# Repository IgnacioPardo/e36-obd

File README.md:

<div align="center">

# E36 OBD

**Read a pre-OBD2 BMW's brain — from a Mac, an iPhone, an Apple Watch, or a board you build yourself.**

A 1994 BMW E36 316i (M43B16, Bosch Motronic 1.7.2) predates OBD2. It speaks **KWP71** over a single-wire **K‑line**, woken with a 5‑baud slow init. A generic OBD2 scan tool can't talk to it at all — not "fewer PIDs", it will *never* establish a session. The usual answer is a Windows laptop running INPA. This isn't that: it's a Mac client, a native iOS/watchOS app, ESP32 firmware, and two open hardware builds — all offline, no Windows, no VM, no third‑party dependencies.

</div>

---

## Four ways to read the car

| | Component | What it is | Where |
|---|---|---|---|
| 🖥️ | **macOS client + web panel** | ~600 lines of Python (stdlib + `pyserial`) driving an FTDI K‑line cable through Apple's built‑in `AppleUSBFTDI` — the 5‑baud wakeup is bit‑banged with the UART's BREAK control. CLI **and** a local web dashboard. | [`e36obd/`](e36obd/) · [client reference](#-macos-client--web-dashboard) |
| 📱 | **iOS + Apple Watch app** | Native SwiftUI BLE dashboard: authentic E36 instruments, a real‑time 3D car, DME fault reading, session recording to SQLite, CSV export, widgets, CarPlay and Live Activities. No servers, no internet. | [`ios/`](ios/) · [details](#-ios--apple-watch-app) |
| 🔌 | **ESP32‑S3 firmware** | MicroPython K‑line ⇄ BLE bridge (Nordic UART) that the app talks to. Plus an Arduino reference sketch and a WiFi/PWA fallback. | [`firmware/`](firmware/) · [details](#-firmware-esp32-s3) |
| 🧩 | **Onboard board (rev B)** | A custom single PCB — ESP32‑S3 + L9637D + AP63203 buck + an OBD2 plug — that plugs straight into the car, in a printed case with a machined‑look **=BMW=** badge. | [`hardware/onboard/`](hardware/onboard/) · [details](#-hardware) |
| 🛠️ | **ELM backpack (rev E)** | A printed enclosure that turns a gutted ELM327 + an ESP32 DevKit into an inline reader — the salvage build the custom board replaces. | [`hardware/elm-backpack/`](hardware/elm-backpack/) · [details](#-hardware) |

---

## Why it's hard (and what was learned on the car)

K‑line‑only BMWs (E36, E38, E39, early E46) expect the diagnostic K‑line on **OBD2 pin 7**, wake on a **5‑baud** address, and run **KWP71**: framed blocks `[length][seq][title][payload…][0x03]` where *every byte but the last* is acknowledged by its bitwise inversion, in both directions. There is no error recovery — one bad byte ends the session.

This was **verified end‑to‑end on a 1994 E36 M43B16 automatic** (2026‑08‑09). The findings that cost the most to discover:

- **The L‑line jumper is mandatory.** A stock K+DCAN cable drives only OBD2 pin 7, but the 1.7‑era DME wants the 5‑baud wakeup on the **L‑line** (OBD2 pin 15). The fix is a solder bridge between **pins 7 and 15** — the instant it was in, address `0x10` answered `55 00 81`. (Watch pin 16: it's +12 V.)
- **Address is `0x10`** (BMW Motronic DME), not `0x12` (that's DS2, a different protocol).
- **Live values only populate with the engine running** — key‑on/engine‑off reads all zeros and looks exactly like a dead link.
- **Sampling is round‑trip bound** at ~1 Hz over 9600 baud, so a log's silence is not proof a sub‑second glitch didn't happen.
- **Reads degrade with the engine running** — ignition noise corrupts the byte handshake, so the live path collapses the core sensors into one contiguous 11‑byte read and rebuilds the session when it breaks.

> 📎 Full pre‑flight electrical checklist, the discovery method for un‑mapping sensors, and protocol notes are in [the client reference below](#-macos-client--web-dashboard) and [`docs/PROTOCOL_NOTES.md`](docs/PROTOCOL_NOTES.md).

---

## 📱 iOS + Apple Watch app

[`ios/E36OBD.xcodeproj`](ios/) — a native SwiftUI dashboard that reads the car over **BLE**, with no server and no internet. iOS 18+, watchOS 11+, **zero third‑party dependencies** (SQLite is the system `libsqlite3`; everything else is Apple's own frameworks).

<table>
<tr>
<td width="60%"></td>
<td width="40%"></td>
</tr>
<tr>
<td align="center"><em>Instruments — the E36 cluster, rebuilt</em></td>
<td align="center"><em>Auto — vehicle, reader state, latest readings</em></td>
</tr>
</table>

**What it does**

Latest development handoff: [session context, design decisions, validation and installation state](docs/sessions/2026-09-11-app-scene-companions.md).

- **Instruments** — the classic 90s BMW cluster in portrait and landscape: load (ms) and tach dials with the red zone, battery/coolant gauges, amber 7‑segment readouts, fan‑out auxiliaries. Needles ease to each reading without interpolating stored samples. Saturated 2550 rpm and empty‑RAM reads are called out as **DME sin datos** rather than shown as real values.
- **Auto** — a real‑time **3D render of the owner's 316i in 295 Samoablau Metallic**, drawn on‑device with RealityKit + Metal. Normal tabs keep the whole car in frame. Expand the scene for free navigation: one finger orbits horizontally and vertically, two fingers pan the camera, and pinch moves from detail close-ups to distant views without auto-fit pushing back. Zoom and pan can be combined; the chosen distance and position survive device rotation. The reset button or double-tap restores the front view, and closing the scene restores protected dashboard framing. Paint, glass and reflections are computed on the phone; the sun button selects studio or outdoor surroundings.
- **Navigation** — Auto, Fallas, Sesiones and Ajustes share one persistent scene, above their content in portrait and beside it in landscape. Each tab is the next quarter-turn around the car; moving back through the bar reverses that ordered orbit, including when tabs are skipped. The scene reaches the screen edge; text and controls retain readable insets. En vivo, Instrumentos and BLE stay at the top. Starting capture keeps the current tab; closing Instruments returns to it. Session selection and unsaved settings survive navigation.
- **Faults** — reads the DME fault memory; pauses and resumes the same recording session around the read.
- **Sessions** — every capture recorded to local SQLite (WAL, file‑protected), browsable with a shared cursor across all five channels and **CSV export** of sensors + events. Gaps are never bridged.
- **Alerts** — configurable thresholds (low load, coolant, intake) with hysteresis, sound and haptics; every episode is logged even when sound is rate‑limited.
- **Widgets · CarPlay · Watch · Live Activities** — *Instrumento E36*, *Garage E36* (with the car render) and *OBC E36* widgets for the Home Screen, StandBy and CarPlay. Garage and OBC also have a large Home Screen size with all five readings; a watchOS companion with five full‑screen gauges and complications; and a Live Activity on the Lock Screen and Dynamic Island. The ESP32 keeps a single BLE link to the phone; everything else is fed from it.

<table>
<tr>
<td></td>
<td></td>
</tr>
</table>

**Architecture.** The tested, platform‑independent core is a local Swift package, [`ios/Core`](ios/Core) (`E36Core`), so the hard parts run without a simulator:

| Module | Responsibility |
|---|---|
| `AcquisitionMachine` | pure state machine for BLE capture (sync → idle → live, faults, DME recovery) |
| `WireProtocol` | frames raw bytes into lines before UTF‑8; parses telemetry vs text |
| `SessionStore` | an `actor` owning the sole SQLite connection; records off the UI/BLE threads; CSV export |
| `AlertEngine` | threshold rules with hysteresis |
| `Models` · `GraphSeries` · `WidgetSnapshot` · `CompanionSnapshot` | sensor model, downsampling that keeps extrema/events, and the bounded snapshots shared to widgets and the watch |

```sh
open ios/E36OBD.xcodeproj          # E36OBD Demo runs on the simulator (scenario picker, no BLE radio)
swift test --package-path ios/Core # 19 core tests, no simulator needed
```

The Xcode project is generated, not hand‑edited — `python3 ios/tools/generate_project.py` regenerates it with the stdlib alone. Deeper docs: **[`ios/DESIGN.md`](ios/DESIGN.md)** (instrument design), **[`ios/VALIDATION.md`](ios/VALIDATION.md)** (QA log), **[`ios/WIDGETS.md`](ios/WIDGETS.md)**, **[`ios/WATCH_AND_LIVE_ACTIVITIES.md`](ios/WATCH_AND_LIVE_ACTIVITIES.md)**, and the 3D pipeline in **[`ios/Design/Vehicle/`](ios/Design/Vehicle/)**.

---

## 🔌 Firmware (ESP32‑S3)

The board runs **MicroPython** (`ESP32_GENERIC_S3‑SPIRAM_OCT`, v1.29.0). On boot, [`firmware/mp/main.py`](firmware/mp/main.py) does `import ble; ble.arrancar()`, starting the BLE loop on its own thread so attaching the REPL doesn't kill it.

| Module | Role |
|---|---|
| [`firmware/mp/kline.py`](firmware/mp/kline.py) | KWP71 transport: 5‑baud slow init, block send/recv with inverted acks, RAM reads, sensor + fault decode. Drives the **ST L9637D** on `TX=GPIO17`, `RX=GPIO18`. DME at **9600 baud** (`0x10`); the automatic gearbox EGS at **4800 baud** (`0x6C`). |
| [`firmware/mp/ble.py`](firmware/mp/ble.py) | The BLE "panel": Nordic UART service, command loop, live streaming, fault reads, session lifecycle and desktop‑grade recovery. |
| [`firmware/mp/web.py`](firmware/mp/web.py) | Optional WiFi SoftAP dashboard (`E36-OBD` / `192.168.4.1`), not started at boot. |
| [`firmware/kline_e36/kline_e36.ino`](firmware/kline_e36/) | An Arduino/C++ reference port of the same protocol — a bring‑up sketch that inits and reads faults once over USB serial. |

**BLE contract** — advertises the **name only** (`E36-OBD`); the app verifies Nordic UART after connecting.

```text
service 6E400001-B5A3-F393-E0A9-E50E24DCCA9E   RX 6E400002-… (write)   TX 6E400003-… (notify)
commands (1 ASCII char): v = live · f = faults · s = stop · ? = help
live line:  D <rpm> <load_ms> <coolant_C> <battery_V> <query_ms> [intake_C]
            D 930 0.70 63.1 13.48 341 23.7
```

Output is CRLF, chunked ≤20 bytes with 12 ms between notifications; intake temp is appended last so older clients stay compatible. **Update firmware over USB** with [`ios/tools/update_ble.py`](ios/tools/update_ble.py) (via `mpremote`) — it backs up every target file, verifies it's really the E36 reader, writes, reads back, and rolls back on any mismatch. It never reflashes MicroPython or touches `main.py`.

Host‑run tests in [`firmware/tests/`](firmware/tests/) exercise the real modules against a scripted fake UART / mocked radio — including a byte‑for‑byte match against the desktop client:

```sh
python3 -B -m unittest discover -s firmware/tests -v
```

---

## 🧩 Hardware

Two open builds, both parametric — a Python source file generates the board or the case, verified by script before export.

### Onboard board — rev B (`hardware/onboard/`)

One 90 × 50 mm two‑layer PCB for JLCPCB SMD assembly: **ESP32‑S3‑WROOM‑1 + L9637D + AP63203 buck + a PCB‑mount OBD2 plug**. 3.3 V straight from the car's 12 V, a hardware low‑battery cutoff (buck EN divider: on at 12.5 V, off at 11.5 V), and it plugs directly into the E36's 20‑pin round connector via a pigtail. `gen_board.py` is the source of truth — placement, nets, zones and the custom OBD2 footprint; `export.py` runs DRC and emits gerbers/BOM/CPL. **DRC: 0 errors.**

<table>
<tr>
<td></td>
<td></td>
</tr>
<tr>
<td align="center"><em>The board — ESP32‑S3 + L9637D + buck + OBD2</em></td>
<td align="center"><em>The case — =BMW= badge, light‑guide LED, USB‑C</em></td>
</tr>
</table>

`case.py` generates a three‑piece printed enclosure (96.8 × 56 × 27 mm): black base and lid with R6 corners, 45° chamfers and a shadow line at the seam, plus a separate **=BMW= badge** copied from the M50 valve cover — black field, 13 fine silver ribs running the length of the lid, the "BMW" plaque set toward the plug and cutting only the middle ribs (one filament change at 1.6 mm, or two colours via AMS). The OBD2 plug's neck is clamped in the end wall, the USB‑C shell passes through a shell‑shaped opening flush with a bezel, LEDs come out through Ø3 mm light pipes, RESET/BOOT are clip holes, and four M3 × 12 screws from below thread into brass heat‑set inserts — nothing visible on the outside. `CASE_PIGTAIL=1` builds the variant without the OBD2 plug for a direct 20‑pin pigtail. See [`hardware/onboard/README.md`](hardware/onboard/README.md) for the full BOM, the schematic, the pinout, the print list and the pre‑fab checklist. ([schematic](hardware/onboard/fab/schematic.png))

### ELM backpack — rev E (`hardware/elm-backpack/`)

The predecessor build: a 162 × 48 × 30.4 mm printed inline enclosure that houses a gutted ELM327 + a buck + an ESP32‑S3 DevKit end‑to‑end, with the same ribbed BMW lid. Fully parametric (`model.py` on build123d), with an offline interactive [CAD viewer](hardware/elm-backpack/viewer.html) and print‑ready 3MF/STL.

Details, the parts list and print settings: [`hardware/elm-backpack/README.md`](hardware/elm-backpack/README.md).

---

## 🖥️ macOS client & web dashboard

Pure Python — stdlib plus `pyserial`. It drives an FTDI **FT232R "INPA compatible K+DCAN"** cable through the OS's own `AppleUSBFTDI` (no vendor kext), bit‑banging the 5‑baud init with the UART's BREAK control. From the repo root:

```bash
python3 -m venv .venv && ./.venv/bin/pip install pyserial   # first time
./.venv/bin/python -m e36obd doctor                         # desk test, no car
```

**Command line** — run in order; each only makes sense once the previous worked:

| Command | What it does |
|---|---|
| `doctor` | Lists serial ports, flags the FTDI one, toggles BREAK, listens 2 s. Silence with no car is fine. |
| `scan` | Tries candidate addresses (`0x10` first) and reports which return a `0x55` sync + keywords. |
| `id` | Prints the ECU identification strings — the real proof of a working link. |
| `codes` | Reads stored fault codes (raw hex; a *speculative* 5‑byte grouping is not a verified decode). |
| `log` | Live values to CSV — `--adc`, `--ram ADDR:LEN`, `--param`, `--interval`, `--duration`, `--out`. |
| `raw` | Sends an arbitrary block title with optional payload — for hunting non‑standard commands. |
| `clear` | Erases fault memory (prompts). **Destroys evidence — read and save codes first.** |

Global flags go **before** the subcommand: `--port`, `--baud` (9600), `--address` (`0x10`), `--loopback auto|on|off`, `-v`. Example: `./.venv/bin/python -m e36obd --address 0x10 -v id`.

**Web dashboard** — `dash` serves a local panel (stdlib + `pyserial`, no framework/CDN, works offline). One thread owns the serial port and drains an action queue between samples, so recording, re‑reading faults, dumping RAM and probing the gearbox coexist with live polling without fighting over the line.

```bash
./.venv/bin/python -m e36obd dash            # http://127.0.0.1:8036
./.venv/bin/python -m e36obd dash --lan      # reachable from the phone, token-guarded
./.venv/bin/python -m e36obd dash --demo     # synthetic data, no car
```

Four hash‑addressable tabs — **Tablero** (analog instruments + 4‑min trend), **Diagnóstico** (decoded faults, DS2 gearbox probe, before/after snapshots), **Capturas** (recorded sessions with a shared cursor and two‑session overlay), **Scanner** (RAM explorer with cumulative change detection). Write and actuator blocks (`0x02` WriteRAM, `0x1A` WriteEEPROM, `0x04` ActivateActuator) are blocked **in the server**, verified against a simulated ECU. There's also a Web Bluetooth **PWA** in [`docs/ble/`](docs/ble/).

<details>
<summary><strong>Pre‑flight electrical checklist</strong> — read this before the cable ever touches the car</summary>

Almost every "it doesn't work" report is one of these three, and all three fail *silently* — the port opens, the command runs, and nothing answers.

1. **OBD2 pins 7–8 must be bridged.** K‑line‑only BMWs expect the K‑line on pin 7; many cables/adapters present it on pin 8. Set the cable's K‑line switch, or solder 7↔8 on its PCB. Verify with a multimeter in continuity: probe pin 7 and pin 8 on the cable's own 16‑pin connector — it should beep.
2. **The 20‑pin adapter must be fully pinned.** The cable is bus‑powered from OBD2 pin 16 (+12 V from the car). Cheap adapters wired K‑line‑and‑ground only leave the FTDI chip unpowered. Confirm it passes at minimum K‑line, +12 V and ground.
3. **Multimeter checks — verify, don't trust.** Confirm the 20‑pin round pinout against a BMW source (TIS / service manual) before probing; several conflicting diagrams circulate. Do continuity with the harness **disconnected from the car**; do voltage at the car's connector with nothing else plugged in.

| Check | Meter mode | Expected |
|---|---|---|
| Battery at the round connector's +12 V pin | DC volts, black on chassis ground | ~12.4 V off, ~13.8–14.4 V running |
| Round K‑line pin → OBD2 pin 7 | Continuity, unplugged from car | Beeps / ~0 Ω |
| Round +12 V pin → OBD2 pin 16 | Continuity, unplugged | Beeps / ~0 Ω |
| Round ground pin → OBD2 pins 4 and 5 | Continuity, unplugged | Beeps on both |
| OBD2 pin 7 → pin 8 on the cable itself | Continuity | Beeps (see §1) |

4. **Ignition position 2.** The DME is only awake with the ignition in position 2 (dash lights on, engine not running). Position 1 is not enough; nothing answers with the key out.

</details>

<details>
<summary><strong>Discovering what the values mean</strong> — ADC channels and the RAM map are un‑mapped</summary>

`log` is a **discovery tool**, not a dashboard: there's no table saying which channel is coolant or where the TPS lives, and raw ADC bytes are not degrees. The method is empirical — change **one** thing with a known physical effect, then find the column that moved the same way.

- **Coolant temp** — log a full sweep through a cold‑start warm‑up; it's the channel that moves *monotonically* over ~10 min then flattens (NTC sensors often fall as temp rises).
- **Throttle** — engine off, ignition on; sweep the pedal. TPS tracks the pedal, returns to rest, and hits a ceiling at wide‑open.
- **Battery** — calibrate absolutely against the multimeter; two points give a linear scale and often hint at the shared ADC reference.
- **Intake air** — responds within seconds to a heat gun, unlike coolant's minutes of lag.

Prefer monotonic or repeatable‑cycle stimuli, load the CSV into anything that plots, then re‑log the interesting channels at a shorter interval. **Nothing here persists a mapping for you — write down what you confirm.**

</details>

<details>
<summary><strong>Troubleshooting</strong></summary>

| Symptom | Likely cause | What to do |
|---|---|---|
| `No serial port found` | Cable not enumerated, or macOS hasn't claimed it | `ls /dev/cu.*`; try another USB port/cable; `system_profiler SPUSBDataType`; pass `--port`. |
| `doctor` opens the port but BREAK fails | `/dev/tty.*` selected instead of `/dev/cu.*`, or a vendor FTDI kext interfering | Always use `/dev/cu.*`; uninstall any vendor FTDI driver and reboot. |
| `scan` finds no responding address | Almost always electrical | Work the pre‑flight list in order before widening the address set. |
| Init OK but blocks fail their ack — `bad ack for byte N` | Timing / line quality, or non‑standard framing | Re‑run with `-v`; try a shorter adapter; if always byte 0, force `--loopback on|off`. |
| Session establishes then dies mid‑`log` | KWP71 drops the link if blocks stop; also a loose‑connection signature | Lower `--interval`, fewer channels; then check the physical connection. |
| Disconnects worse with the engine running | Ignition noise on a single‑wire bus, or a sagging supply | Route away from plug leads/coil; verify pin‑16 voltage running; clean ground. |
| `NOT_SUPPORTED` | BMW used a different block title | Probe with `raw --title 0xNN`. |

</details>

<details>
<summary><strong>Known vs unknown</strong> — how much to trust the output</summary>

**Solid:** KWP71 framing and acks (from [colinbourassa/libiceblock](https://github.com/colinbourassa/libiceblock)); the macOS BREAK‑banged 5‑baud init (absolute bit deadlines, the port never leaves 9600); loopback auto‑detection.

**Not confirmed:** exact block titles may be non‑standard per manufacturer; the fault‑code record layout and code→description mapping are **not** decoded (a code number without a table tells you a fault exists, not what it is); ADC channel meanings, the RAM map and scaling are unknown and must be derived. `raw` and `log` exist precisely to explore this.

</details>

---

## Repository layout

```
e36obd/         macOS client + web dashboard (Python: stdlib + pyserial)
firmware/       ESP32-S3 firmware — mp/ (MicroPython, shipping) + kline_e36/ (Arduino ref) + tests/
ios/            SwiftUI iOS + watchOS app — E36OBD.xcodeproj, Core/ (E36Core package), Design/Vehicle/ (3D)
hardware/       onboard/ (rev B custom PCB + case) · elm-backpack/ (rev E enclosure) · wiring diagrams
docs/           PROTOCOL_NOTES.md, EGS_NOTES.md, GAUGE_DESIGN.md, cableado.html, ble/ (Web Bluetooth PWA)
sessions/       archived AI-assisted development transcripts (Git LFS)
```

Large binary assets (`.usdz`, `.blend`, `.glb`, `.exr`, `.step/.stl/.3mf`, `.pdf`, session logs) are tracked with **Git LFS** — install [git‑lfs](https://git-lfs.com) and `git lfs pull` to fetch them.

## Safety

- **Do not probe pins at random with the ignition on.** Shorting a DME input to +12 V or ground can destroy it, and not every line is fuse‑protected. An M1.7.2 is expensive and increasingly rare.
- Do continuity testing with the harness **disconnected from the car**; do voltage testing one pin at a time against a known‑good ground.
- **Verify the round‑connector pinout against a BMW source before touching a probe to it.** Assume any diagram — including in this repo — is wrong until you've checked it. Beware pin 16 (+12 V) next to the K‑line.
- **`clear` and fault‑memory erase destroy evidence.** Read and save codes first; the web panel always snapshots before erasing.
- `raw` sends arbitrary block titles to a live engine controller. `WRITE_RAM`, `WRITE_EEPROM` and `ACTIVATE_ACTUATOR` are not read‑only. Know what a title does before sending it.
- Do first‑contact work engine‑off. Once logging with the engine running, keep the cable clear of the belts, fan and exhaust manifold.

---

<div align="center">
<sub>Personal project for a specific 1994 E36 316i (M43B16). No affiliation with BMW; "BMW" marks belong to their owner and the badge/branding here are for a personal build. No formal license — ask before reuse.</sub>
</div>

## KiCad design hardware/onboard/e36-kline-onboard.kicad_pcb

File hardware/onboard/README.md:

# E36 K-line — una sola placa (rev B)

ESP32-S3-WROOM-1 + L9637D + buck AP63203 + ficha OBD2 macho, todo en una PCB de **90 × 50 mm**,
dos capas, para mandar a JLCPCB con ensamblado SMD. Reemplaza al conjunto "ELM327 destripado +
DevKitC-1 + módulo buck" y a la placa `../kline-frontend.kicad_pcb` (que dejaba el MCU afuera).

| Archivo | Qué es |
|---|---|
| `gen_board.py` | **La fuente.** Colocación, redes, clases de pista, footprint OBD2, zonas, serigrafía. Genera la placa. |
| `e36-kline-onboard.kicad_pcb` / `.kicad_pro` | Placa generada y ruteada (abrir en KiCad 10). |
| `e36obd.pretty/OBD2_Male_RightAngle_16P.kicad_mod` + `fp-lib-table` | Footprint propio de la ficha OBD2. |
| `gen_schematic.py` → `schematic.svg`, `e36-kline-onboard.net` | Esquema y netlist, generados de **las mismas redes** que la placa y verificados contra ellas. |
| `export.py` → `fab/` | DRC, gerbers (`e36-kline-onboard-gerbers.zip`), `bom-jlcpcb.csv`, `cpl-jlcpcb.csv`, renders. |
| `pricing.py` → `fab/pricing-jlcpcb.md` | Estimación de precio JLCPCB (API de partes + tarifas publicadas): partes, fijos, totales por cantidad. |
| `pcbway.py` → `fab/pcbway/`, `fab/pcbway-sample-order.zip` | Paquete de pedido PCBWay para 1 muestra ensamblada: BOM en su formato con MPN, centroides, dibujo de armado, notas y parámetros del formulario. |
| `case.py` → `case/` | Caja de dos piezas (STL listos para imprimir, STEP, ensamble con referencias). |
| `render_case.py` → `case/render-*.png` | Renders en Blender de la caja con la placa real (GLB exportado por kicad-cli) adentro. |

Estado: **DRC 0 errores, 0 desconexiones** (KiCad 10.0.5). Quedan solo avisos de serigrafía
(referencias de 0603 que pisan pads); JLC los recorta solos.

## Qué hay en la placa

```
 OBD2 16 ─ F1 1A ─┬─ D1 TVS SMBJ24A ─ GND
                  ├─ R1 510R ─ K ─── OBD2 7 y 15 ──┐
                  ├─ U1 L9637D VS        K ────────┘   RX → GPIO18   TX ← GPIO17
                  ├─ R2 100k / R3 22k ── V_SENSE → GPIO4 (ADC1)
                  ├─ R10 36k / R11 3k74 ─ EN del buck (UVLO: ON 12,5 V, OFF 11,5 V)
                  └─ D2 SS34 ─┬─ VIN ─ U2 AP63203 ─ L1 4.7µH ─ 3V3 ─ ESP32-S3-WROOM-1-N16R8
 USB-C VBUS ─ D3 SS34 ────────┘  └ R12 4k7 → EN (con USB arranca siempre)   │
 USB-C D+/D- ─────────────────────────────────────────── GPIO20/19 ┘
 J4 (cola al redondo de 20): 1 GND · 2 K · 3 +12   — en paralelo con la ficha OBD2
```

- **3,3 V directo desde los 12 V**, sin riel de 5 V. El único consumidor de 5 V era el DevKit.
  El AP63203 (3,8–32 V de entrada, 2 A, salida fija 3,3 V, 1,1 MHz) alimenta módulo y L9637D.
  FB va directo a 3V3 (versión de salida fija).
- **Corte por batería baja, en hardware.** El pin EN del buck tiene umbral de precisión (1,18 V
  sube / 1,10 V baja) y dos fuentes de corriente internas (1,5 µA fija + 4 µA de histéresis).
  Con R10 = 36k desde VBAT_F y R11 = 3,74k a GND (Eq. 1 y 2 de la hoja de datos) el buck
  **arranca a 12,5 V y corta a 11,5 V**: con el motor andando (13,1–14,4 V) está siempre
  encendido; con el motor parado sigue hasta que la batería baja a 11,5 V y ahí se apaga solo,
  quedando el consumo en ~1 mA (1 µA del buck apagado + los divisores + el reposo del L9637D).
  R12 = 4k7 desde VBUS fuerza EN por encima del umbral: **con USB arranca siempre**, haya auto
  o no. La ventana entre batería en reposo (12,6–12,8 V) y alternador flojo (13,1 V) es
  demasiado angosta para detectar "motor parado" solo con resistencias, así que el corte
  duro es el piso de seguridad: lo que evita el drenaje diario es el **deep sleep por
  V_SENSE** en el firmware (dormir por debajo de ~12,9 V unos minutos, despertar y medir).
  Para otros umbrales: `R10 = (0,932·VON − VOFF)/4,1 µA`, `R11 = 1,1·R10/(VOFF − 1,1 + 5,5 µA·R10)`.
- **USB-C solo para programar y para el banco**: VBUS y los 12 V del auto se OR-ean por D2/D3 hacia
  VIN. Con el auto y la notebook enchufados a la vez mandan los 12 V; nada vuelve a la notebook.
  Sin auto, la línea K y V_SENSE están muertas; el ESP32 arranca igual.
- **L9637D** igual que el prototipo que funcionó: VCC a 3,3 V (mínimo 3 V, lógica compatible
  sin conversor), VS a los 12 V filtrados, K a los pines **7 y 15** (el DME despierta por L).
  R1 510 Ω es el pull-up de K a VS que exige la hoja de datos. A 14 V disipa 0,38 W mientras K
  está baja, así que va en **2010** (0,75 W), no en 0805 como en la placa anterior.
- **D1 con la banda hacia +12 V.** En `../kline-frontend` el TVS estaba al revés en el netlist
  (ánodo a +12 V): conduciría a 0,7 V y volaría el fusible. Acá pad 1 (cátodo) = VBAT_F.
  Polaridad invertida del auto → el TVS conduce en directo y F1 corta. Ese es el mecanismo.
- **Sensado de batería**: 100k/22k → 16 V = 2,88 V en GPIO4. `V = 3,3 × adc/4095 × 122/22`.
  El firmware de hoy no lo lee (la tensión viene del DME por K); queda para dormir el módulo
  cuando el motor está parado — el pin 16 es +12 V **permanente**.
- **Módulo entero sobre la placa**, con la antena en el borde superior y una zona prohibida
  (sin cobre, pistas ni vías en las dos caras) de 53–90 × 0–6,5 mm: la opción 2 de la guía de
  Espressif. Se eligió para que la caja sea un prisma liso; la opción 1 (antena colgando) rinde
  algo mejor pero obliga a un saliente. La pared de la caja frente a la antena no puede ser
  metálica ni con carga de carbono.
- **Directo al conector redondo de 20 pines del E36, sin adaptador.** J4 es una JST-XH de 3 vías en
  paralelo con la ficha OBD2: 1 GND, 2 K, 3 +12 V. Se le suelda una cola cortada de un adaptador
  20→OBD2 (o un macho de 20 con cables): **19 → GND, 15+17+20 juntos → K, y el +12 de 16 (KL15,
  ignición) o de 14 (KL30, batería)**. Tomando el +12 del **pin 16** la placa se apaga con la
  llave y el drenaje de batería desaparece del todo; el OBD2 no tiene ese pin, por eso ahí hace
  falta el UVLO y el deep sleep. El macho de 20 no existe para montar en PCB: va por cable. Para
  ese uso, `CASE_PIGTAIL=1 case.py` genera la caja con la pared cerrada y un pasacable de 7 mm en
  vez de la muesca de la ficha.
- **USB: solo el nativo (GPIO19/20), sin puente CH340/CH9102.** Es el puerto "USB" del DevKit, no
  el "COM": MicroPython, `mpremote` y la REPL andan sin tocar nada; grabar la imagen de MicroPython
  exige BOOT apretado al resetear (una vez). Se evaluó poner un CH340C con auto-reset y se descartó
  por innecesario.
- EN: 10k + 1 µF + botón RESET. IO0: 10k + botón BOOT. Programación por el USB nativo
  (GPIO19/20) o por J2 (UART0, sin poblar; pines **EN IO0 TX0 RX0 GND 3V3**). LED verde = 3V3;
  LED ámbar en **GPIO38** (el mismo del RGB del DevKitC-1 v1.1, así el firmware no cambia de pin).

### Pines del ESP32 que usa el firmware

| GPIO | Función | Pin del módulo |
|---|---|---|
| 17 | K_TX → L9637D TX (UART1 + bit-bang del init a 5 baudios) | 10 |
| 18 | K_RX ← L9637D RX | 11 |
| 4 | V_SENSE (ADC1_CH3, funciona con WiFi) | 4 |
| 38 | LED de estado (ámbar) | 31 |
| 0 | BOOT (botón, pull-up 10k) | 27 |
| 19 / 20 | USB D− / D+ | 13 / 14 |
| 43 / 44 | TXD0 / RXD0 → J2 | 37 / 36 |

`firmware/mp/kline.py` sigue con `TX_PIN = 17`, `RX_PIN = 18`: no cambia nada.
En la N16R8 los GPIO 33–37 son de la PSRAM y no se usan.

## La ficha OBD2

Es un macho J1962 acodado de montaje en PCB — el mismo formato que usan los ELM327 y el
**Macchina CCBDM20**. El footprint se construyó desde el STEP y el plano de ese conector,
no de una foto:

| Dato | Valor |
|---|---|
| Paso entre pines de una fila | **4,00 mm** |
| Separación entre filas | **3,00 mm** |
| Fila 1–8 (la de abajo en la cara de enchufe, lado ancho de la D) | 2,25 mm detrás de la brida |
| Fila 9–16 | 5,25 mm detrás de la brida |
| Pata de soldadura | 0,9 × 0,8 mm, ~2,2 mm de largo → agujero 1,3 mm, pad 2,1 mm |
| Cuerpo | 40,3 mm de ancho, todo fuera de la placa; la brida apoya en el borde |

El borde izquierdo de la placa es el plano trasero de la brida. Pin 1 arriba (y = 10 mm),
pin 8 abajo; pines 9–16 en la segunda fila. Solo 4, 5 (GND), 7 (K), 15 (L) y 16 (+12 V) van
a algo; los otros once pads quedan sueltos.

**Antes de soldar el conector**, con la placa sin enchufar al auto, medir continuidad entre
la cara de enchufe y los pads: el pin 16 del macho (esquina, fila de abajo con el lado ancho
arriba, extremo izquierdo mirando los pines) tiene que llegar al pad marcado 16. Si el
conector que compraste está espejado respecto del CCBDM20, el error es **benigno**: +12 V
caería en el pad 9 (sin conectar) y la placa simplemente no encendería. Nada se quema.

## Antes de mandar a fabricar

**Precio** (estimado con `pricing.py`, 2026-09-11, ensamblado económico, sin envío): unas **97 USD por 5 placas
(≈19 c/u)** o **140 USD por 10 (≈14 c/u)**; los fijos son 43 USD (setup 8,18 + stencil 1,53 + 11 partes
extendidas × 3,07) y las partes ≈10 USD por placa, de los cuales el módulo son 5. Detalle en
[`fab/pricing-jlcpcb.md`](fab/pricing-jlcpcb.md). La ficha OBD2 va aparte (sin stock en JLC). Para **una sola muestra
con la ficha soldada por la fábrica**, PCBWay: paquete listo en `fab/pcbway/` (`ORDER-NOTES.md` tiene los valores del
formulario y el texto de instrucciones). **Cotización oficial** del motor de PCBWay (`fab/pcbway/quote-official.md`):
PCB 5 pcs 6,50 USD + ensamblado 1 placa 88,00 USD (tarifa plana) + envío FedEx 48,87 / DHL 72,73; componentes
aparte (≈15–25 USD): ≈160–170 USD la muestra.

1. **Números LCSC.** Los marcados `verificar` o `C?` en `fab/bom-jlcpcb.csv` hay que
   confirmarlos en la librería de JLC al momento de pedir: L9637D (C130489), módulo
   ESP32-S3-WROOM-1-**N16R8** (C2913202), inductor SWPA6045S4R7MT (C78804), TVS SMBJ24A,
   capacitores 1210 10 µF/50 V X7R, la 2010 de 510 Ω y la 0603 de 3,74k (E96). El resto son
   básicos de JLC.
2. **Variante del módulo.** El firmware cargado es `ESP32_GENERIC_S3-SPIRAM_OCT`: necesita
   PSRAM octal → **N16R8** (o N8R8). Una N16 sin R8 arranca pero ese build no.
3. **Ficha OBD2.** J1 es THT: soldarla a mano (patas cortas, estañar desde abajo) o pedir el
   ensamblado TH de JLC (`C9900166046`, "OBD-II-16P-Male-90-Deg", sin plano público:
   verificar su footprint contra la tabla de arriba antes de confiar).
4. **Capacidades JLC**: 2 capas, 1,6 mm, 1 oz. Pista mínima usada 0,187 mm (los cuellos que
   deja Freerouting en los pines finos), holgura mínima 0,15 mm, vía 0,7/0,35, taladro mínimo
   0,3. Todo dentro de lo estándar (0,127 mm / 0,3 mm).
5. **En la vista previa de JLC** revisar la rotación de lo polarizado: D1, D2, D3 (banda),
   LED1/LED2, U1 (pin 1), U2, U3. El CPL sale con el origen en la esquina inferior izquierda.
6. J2 no se puebla (está fuera del BOM y del CPL).
7. La caja es `case.py` (sección **La caja**); la `../elm-backpack` no sirve para esta placa.
8. Si vas directo al conector de 20 pines, no hace falta soldar la ficha OBD2 (J1): con J4 y la
   cola alcanza, y la caja `-pigtail` cierra esa pared.

## La caja

`case.py` (build123d, `~/Desktop/E36_OBD/.cadenv/bin/python hardware/onboard/case.py`) genera
en `case/` una caja de **tres piezas** para **esta** placa, con las mismas coordenadas de
`gen_board.py`: base y tapa en negro y el **emblema =BMW= aparte, en plata**, que encaja a ras
en un cajeado de la tapa. La `../elm-backpack` no sirve: era para las placas sueltas.

| | |
|---|---|
| Exterior | **96,8 × 56,0 × 27,0 mm**, prisma liso, más los 16 mm del conector |
| Forma | esquinas verticales R6, chaflán de 45° de 2 mm en el borde de la tapa y de 1,5 mm en el del piso, línea de sombra de 0,5 mm en la junta; tapa lisa |
| Paredes / piso / tapa | 2,4 / 2,4 / 3,0 mm; la pared del conector 1,5 mm |
| Interior sobre la placa | 17 mm — lo fija la brida del conector (15,6 mm), no la electrónica (máx. 5 mm) |
| Sujeción | 4 × **M3 × 12** desde abajo, cabeza embutida; pasan por los separadores (3 mm) y la placa y roscan en **insertos M3 termofijados** (latón, Ø4,6 × 4,6; agujero impreso Ø4,0 × 5,5) en los postes Ø7,5 de la tapa. Sin tornillos a la vista |
| Variante | `CASE_PIGTAIL=1`: sin muesca para la ficha OBD2, pared izquierda cerrada con pasacable Ø7 para la cola al conector de 20 (`base-pigtail.stl`, `lid-pigtail.stl`) |
| Conector OBD2 | la pared entra en el **cuello de 2 mm** del conector: la brida queda adentro, el cuerpo afuera. La muesca está abierta hacia arriba para bajar la placa; la lengüeta de la tapa la cierra |
| USB-C | **la ficha atraviesa la pared**: sobresale 1,6 mm del borde de la placa y pasa por una abertura con la forma de su blindaje (estadio 9,4 × 3,6, 0,22 de juego por lado) en una pared local de 1,3 mm; la boca queda a ras del fondo de un bisel de 18 × 10 donde entra el sobremoldeado del cable. Una repisa de 1,2 mm bajo el borde de la placa toma el empuje del enchufe |
| Antena | queda dentro, contra la pared trasera: esa pared no puede ser metálica ni con carga de carbono |
| Botones | agujeros Ø2 sobre RESET y BOOT: se pulsan con un clip, no hay botones a la vista (BOOT se movió en la placa a (77,5, 39) para dejar libre la banda del emblema) |
| LEDs | dos **guías de luz**: varilla acrílica Ø3 × 16 mm pegada desde adentro en un agujero Ø3,1 con tope a 0,5 mm de la cara (se ve un punto de Ø2,4) |
| Emblema | pieza aparte `badge.stl`, **85 × 22 × 1,6 mm**, copiada de la tapa M50: campo negro, **13 nervios finos** (0,8 mm de ancho, paso 1,6) que corren a lo largo, y la placa "BMW" **corrida hacia la ficha**, de 12 mm de alto: interrumpe solo los siete nervios del medio; los tres de arriba y los tres de abajo siguen enteros a lo largo, como en el motor. Nervios y letras en relieve de 0,8 mm en plata: se imprime relieve arriba con un **cambio de filamento en la capa de 1,6 mm** (negro → plata) o en dos colores con el AMS. Entra a ras en el cajeado de la tapa con 0,15 de juego por lado; se pega con cianoacrilato |
| Piso | grabado "E36 K-LINE rev B" y el pinout OBD2 |
| Otros | 7 respiraderos por lado (2 × 8 mm), dos ranuras 3 × 12 en el piso para un precinto |

Archivos: `base.stl` (piso abajo), `lid.stl` (**ya dada vuelta**, cara exterior abajo), `badge.stl`
(relieve arriba), `base.step`, `lid.step` (en coordenadas de montaje) y `assembly.step` con la placa,
el módulo, el conector (cuerpo en D real) y los volúmenes de los componentes más altos como referencia.
Los renders (`render_case.py`, Blender EEVEE con tres soles y piso) muestran la ficha OBD2 con su
forma en D. Renders: `render_case.py` (Blender 4.5,
Workbench) mete el GLB de la placa (`kicad-cli pcb export glb --drill-origin`) en la caja y saca
`render-assembled/open/board/rear/connector-end.png`. El conector se dibuja como bloque: no hay
modelo 3D libre del CCBDM20 en KiCad.

Verificado por el script: cada pieza es un sólido válido y ninguna interfiere con la placa, el
módulo, la brida/cuello/cuerpo del conector, el USB-C, los botones, el inductor, el TVS ni los
pads de la ficha (la muesca del conector pasa la prueba con 0,15 mm hacia el cuerpo y 0,35 hacia la
brida), y el emblema no toca la tapa. Los chaflanes de 45° se imprimen sin soporte en las dos
piezas (cara exterior contra la cama en la tapa). **No verificado**: el juego real del cuello contra un conector medido, la tolerancia de tu
impresora en los pilotos de 2,6 mm y en el labio de 0,3 mm, y la temperatura en vano motor (ASA).

Imprimir: 0,4 mm, 0,2 mm de capa, 4 paredes; base piso abajo, tapa cara exterior abajo (los
grabados quedan contra la cama, como en la elm-backpack), emblema como viene (relieve arriba, en
plata; con 0,12 mm de capa queda más fino). Sin soportes salvo, si hace falta, el techo de la
abertura USB. Después: cuatro insertos M3 con el soldador en los postes de la tapa, dos varillas
acrílicas Ø3 cortadas a 16 mm en los agujeros de los LEDs, y el emblema pegado en su cajeado.

## Lo que no se verificó

- **Encaje físico del conector.** Sale de un STEP, no de un conector medido. Antes de soldar,
  apoyar el conector sobre la placa y ver que las 16 patas entren.
- **Ruteo automático.** Freerouting (2.4.1, 30 pasadas) hizo las pistas; yo fijé colocación,
  anchos por clase (potencia 0,8 mm, K 0,5, USB 0,2, señal 0,25) y 80 vías de costura de GND.
  El lazo del buck es corto (SW → L1 a 2,4 mm) pero no está optimizado a mano.
- **Térmica en vano motor.** AP63203 hasta 125 °C de juntura; módulo −40…85 °C ambiente.
  Nadie midió la temperatura donde va a vivir.
- **Consumo con motor parado.** ~40–100 mA continuos del módulo despierto = 1–2,4 Ah/día de la
  batería. Es firmware (deep sleep por V_SENSE), no placa.

## Regenerar

```sh
PY=/Applications/KiCad/KiCad.app/Contents/Frameworks/Python.framework/Versions/3.9/bin/python3
$PY hardware/onboard/gen_board.py                # colocación + redes + zonas, sin pistas
FREEROUTING=/tmp/fr/freerouting.jar PASSES=30 \
$PY hardware/onboard/gen_board.py --route        # exporta DSN, rutea, importa SES, cose GND
$PY hardware/onboard/export.py                   # DRC, gerbers, BOM, CPL, renders en fab/
python3 hardware/onboard/gen_schematic.py        # schematic.svg + .net verificados contra N
```

Freerouting: `curl -L -o /tmp/fr/freerouting.jar https://github.com/freerouting/freerouting/releases/download/v2.4.1/freerouting-2.4.1.jar`
(necesita Java 21+; con `-mt 1` para que el optimizador no genere violaciones de holgura).

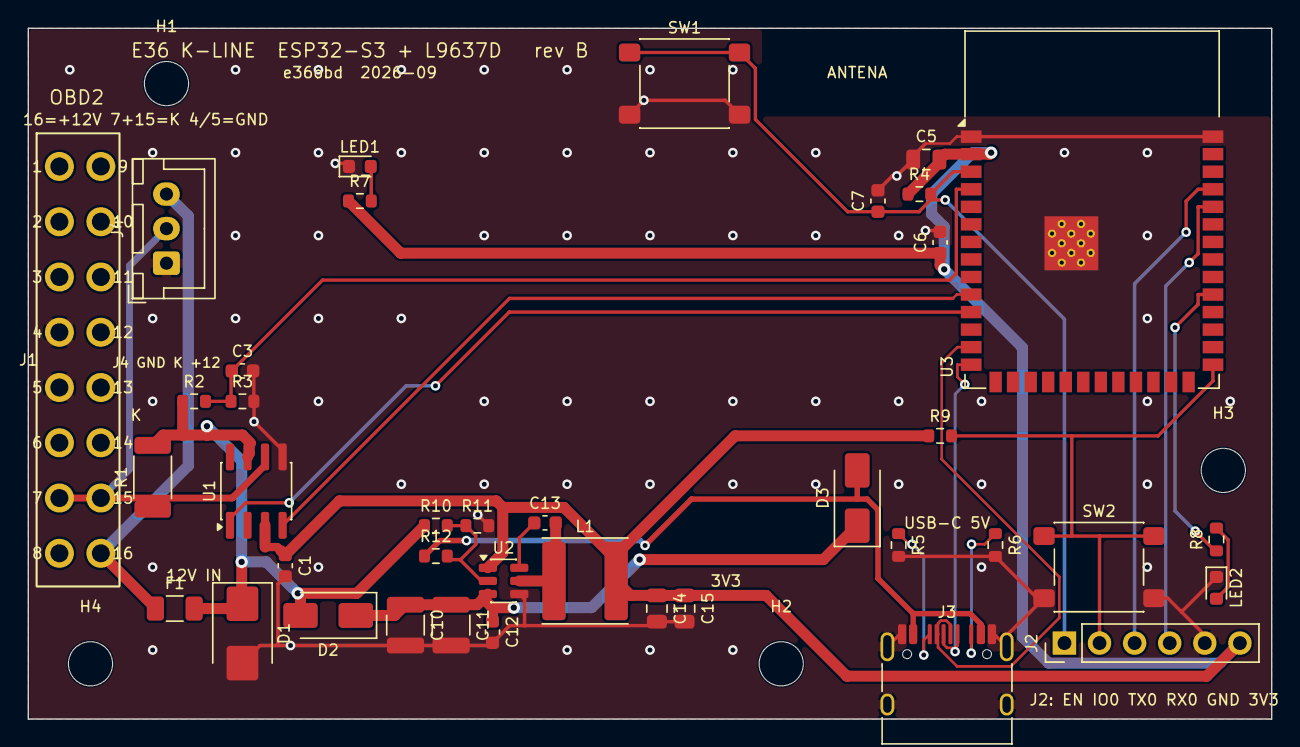
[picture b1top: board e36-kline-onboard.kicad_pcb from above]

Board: 2 copper layers, 90.0 x 50.0 mm, 43 parts (0 on the bottom side), 24 nets.

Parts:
C1, C3, C6, C13: 100n; C_0603_1608Metric
C5: 10u; C_0805_2012Metric
C7: 1u; C_0603_1608Metric
C10, C11: 10u 50V; C_1210_3225Metric
C12: 100n 50V; C_0603_1608Metric
C14, C15: 22u 10V; C_0805_2012Metric
D1: SMBJ24A; D_SMB
D2, D3: SS34; D_SMA
F1: 1A 32V; Fuse_1206_3216Metric
H1, H2, H3, H4: M3; MountingHole_3.2mm_M3
J1: OBD2-M-90; OBD2_Male_RightAngle_16P
J2: DEBUG; PinHeader_1x06_P2.54mm_Vertical
J3: USB-C 16P; USB_C_Receptacle_HRO_TYPE-C-31-M-12
J4: PIGTAIL; JST_XH_B3B-XH-A_1x03_P2.50mm_Vertical
L1: 4.7uH 3.3A; L_Sunlord_SWPA6045S
LED1: PWR blanco; LED_0603_1608Metric
LED2: STATUS rojo; LED_0603_1608Metric
R1: 510R 0.75W; R_2010_5025Metric
R2: 100k; R_0603_1608Metric
R3: 22k; R_0603_1608Metric
R4, R9: 10k; R_0603_1608Metric
R5, R6: 5k1; R_0603_1608Metric
R7: 2k2; R_0603_1608Metric
R8: 1k; R_0603_1608Metric
R10: 36k; R_0603_1608Metric
R11: 3k74; R_0603_1608Metric
R12: 4k7; R_0603_1608Metric
SW1: RESET; SW_SPST_PTS645Sx43SMTR92
SW2: BOOT; SW_SPST_PTS645Sx43SMTR92
U1: L9637D; SOIC-8_3.9x4.9mm_P1.27mm
U2: AP63203; TSOT-23-6
U3: ESP32-S3-WROOM-1-N16R8; ESP32-S3-WROOM-1

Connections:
+3V3: C1.1, C5.2, C6.1, C14.1, C15.1, J2.6, L1.2, R4.1, R7.1, R9.1, U1.3, U2.1, U3.2
BST: C13.1, U2.6
CC1: J3.A5, R5.1
CC2: J3.B5, R6.1
EN: C7.1, J2.1, R4.2, SW1.1, U3.3
EN_BUCK: R10.2, R11.1, R12.2, U2.2
GND: C1.2, C3.2, C5.1, C6.2, C7.2, C10.2, C11.2, C12.2, C14.2, C15.2, D1.2, J1.4, J1.5, J2.5, J3.A1, J3.A12, J3.SH, J4.1, LED1.1, LED2.1, R3.2, R5.2, R6.2, R11.2, SW1.2, SW2.2, U1.5, U2.4, U3.1, U3.40, U3.41
IO0: J2.2, R9.2, SW2.1, U3.27
IO38: R8.1, U3.31
K_LINE: J1.7, J1.15, J4.2, R1.1, U1.6
K_RX: U1.1, U3.11
K_TX: U1.4, U3.10
LED1_A: LED1.2, R7.2
LED2_A: LED2.2, R8.2
RXD0: J2.4, U3.36
SW: C13.2, L1.1, U2.5
TXD0: J2.3, U3.37
USB_DN: J3.A7, J3.B7, U3.13
USB_DP: J3.A6, J3.B6, U3.14
VBAT_F: D1.1, D2.2, F1.2, R1.2, R2.1, R10.1, U1.7
VBAT_RAW: F1.1, J1.16, J4.3
VBUS: D3.2, J3.A4, J3.A9, R12.1
VIN: C10.1, C11.1, C12.1, D2.1, D3.1, U2.3
V_SENSE: C3.1, R2.2, R3.1, U3.4

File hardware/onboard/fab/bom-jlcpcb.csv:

Comment,Designator,Footprint,LCSC Part #,MPN,Nota
OBD2-M-90,J1,OBD2_Male_RightAngle_16P,C9900166046 (JLC TH) verificar,CCBDM20 / J1962 male 90deg PCB,"paso 4.0, filas 3.0"
1A 32V,F1,Fuse_1206_3216Metric,C183160,S1206-S-1.0A (Sart),fusible 1206 (extendido)
SMBJ24A,D1,D_SMB,C123819,SMBJ24A,"TVS unidireccional, catodo (banda) a +12V"
SS34,"D2,D3",D_SMA,C8678,SS34,OR de entrada 12V -> VIN
510R 0.75W,R1,R_2010_5025Metric,C175041,CR2010F510RE04Z,"pull-up K a VS, 0,3 W pico"
L9637D,U1,SOIC-8_3.9x4.9mm_P1.27mm,C153038,E-L9637D013TR,"transceptor ISO9141 (ST, ECOPACK)"
100n,"C1,C3,C13,C6",C_0603_1608Metric,C14663,0603 100nF 50V X7R,desacople VCC U1
100k,R2,R_0603_1608Metric,C25803,0603 100k 1%,"divisor V_SENSE, rama alta"
22k,R3,R_0603_1608Metric,C31850,0603 22k 1%,"divisor V_SENSE, rama baja"
AP63203,U2,TSOT-23-6,C780769,AP63203WU-7,"buck 3.3V 2A, 3.8-32V"
10u 50V,"C10,C11",C_1210_3225Metric,C53084458,CC1210X7R50V106MN,CIN
100n 50V,C12,C_0603_1608Metric,C14663,0603 100nF 50V,CIN hf
4.7uH 3.3A,L1,L_Sunlord_SWPA6045S,C78804,SWPA6045S4R7MT,inductor buck
22u 10V,"C14,C15",C_0805_2012Metric,C45783,0805 22uF 10V X5R,COUT
USB-C 16P,J3,USB_C_Receptacle_HRO_TYPE-C-31-M-12,C165948,TYPE-C-31-M-12,programacion / banco
5k1,"R5,R6",R_0603_1608Metric,C23186,0603 5.1k,CC1 pull-down
ESP32-S3-WROOM-1-N16R8,U3,ESP32-S3-WROOM-1,C2913202,ESP32-S3-WROOM-1-N16R8,"antena sobre la placa, zona sin cobre"
10u,C5,C_0805_2012Metric,C15850,0805 10uF 10V,desacople 3V3 modulo
10k,"R4,R9",R_0603_1608Metric,C25804,0603 10k,pull-up EN
1u,C7,C_0603_1608Metric,C15849,0603 1uF 10V,RC de EN
RESET,SW1,SW_SPST_PTS645Sx43SMTR92,C318884,TS-1187A-B-A-B / PTS645,reset (EN a GND)
BOOT,SW2,SW_SPST_PTS645Sx43SMTR92,C318884,TS-1187A-B-A-B / PTS645,IO0 a GND
PWR blanco,LED1,LED_0603_1608Metric,C2290,KT-0603W,3V3 presente (blanco: el unico 0603 basico junto al rojo)
2k2,R7,R_0603_1608Metric,C4190,0603 2.2k,LED1
STATUS rojo,LED2,LED_0603_1608Metric,C2286,KT-0603R,IO38
1k,R8,R_0603_1608Metric,C21190,0603 1k,LED2
36k,R10,R_0603_1608Metric,C23147,0603WAF3602T5E,"UVLO buck, rama alta (Eq.1 AP63203) (extendido)"
3k74,R11,R_0603_1608Metric,C23016,0603WAF3741T5E,"UVLO buck, rama baja: ON 12,5 V / OFF 11,5 V (extendido)"
4k7,R12,R_0603_1608Metric,C23162,0603 4.7k,VBUS fuerza EN: en el banco arranca igual
PIGTAIL,J4,JST_XH_B3B-XH-A_1x03_P2.50mm_Vertical,C144394,B3B-XH-A(LF)(SN),cola al redondo de 20: 1 GND(19) 2 K(15+17+20) 3 +12(16 KL15 o 14 KL30)

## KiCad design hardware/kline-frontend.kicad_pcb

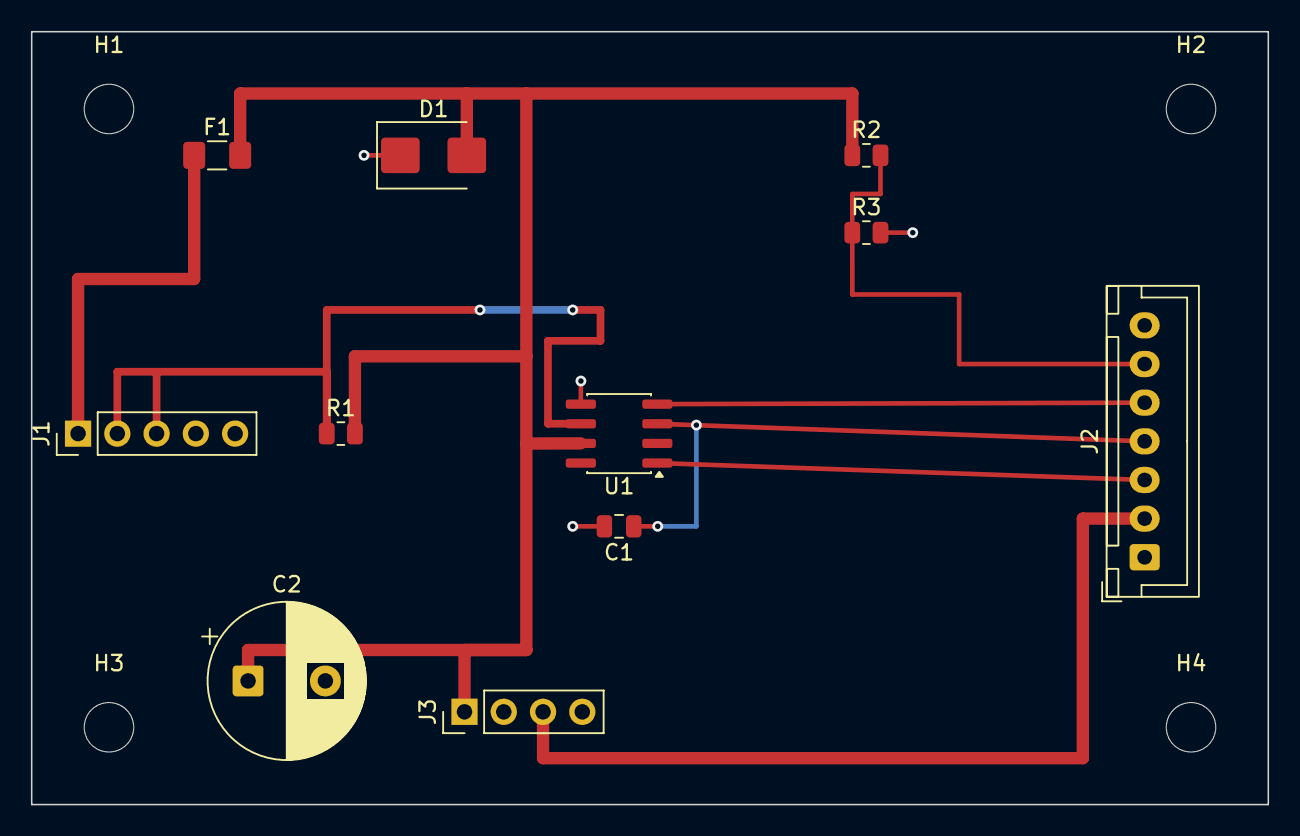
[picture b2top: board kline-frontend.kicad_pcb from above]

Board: 2 copper layers, 80.0 x 50.0 mm, 15 parts (0 on the bottom side), 9 nets.

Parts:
C1: 100n; C_0805_2012Metric
C2: 470u/50V; CP_Radial_D10.0mm_P5.00mm
D1: SMBJ26A; D_SMB
F1: 1A; Fuse_1206_3216Metric_Pad1.42x1.75mm_HandSolder
H1, H2, H3, H4: M3; MountingHole_3.2mm_M3
J1: OBD2-5; PinHeader_1x05_P2.54mm_Vertical
J2: MCU-7; JST_XH_B7B-XH-A_1x07_P2.50mm_Vertical
J3: BUCK; PinHeader_1x04_P2.54mm_Vertical
R1: 510R; R_0805_2012Metric
R2: 100k; R_0805_2012Metric
R3: 22k; R_0805_2012Metric
U1: L9637D; SOIC-8_3.9x4.9mm_P1.27mm

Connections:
+3V3: C1.1, J2.4, U1.3
+5V: J2.2, J3.3
GND: C1.2, C2.2, D1.1, J1.4, J1.5, J2.1, J2.7, J3.2, J3.4, R3.2, U1.5
K_LINE: J1.2, J1.3, R1.1, U1.6
K_RX: J2.3, U1.1
K_TX: J2.5, U1.4
VBAT_FUSED: C2.1, D1.2, F1.2, J3.1, R1.2, R2.1, U1.7
VBAT_RAW: F1.1, J1.1
V_SENSE: J2.6, R2.2, R3.1

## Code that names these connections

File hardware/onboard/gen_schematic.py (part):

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box("J1", 40, 150, 130, 330, "OBD2 macho", [("16", "R", 60, "16 +12V"), ("7", "R", 120, "7 K"), ("15", "R", 150, "15 L"),
                                             ("4", "R", 240, "4 GND"), ("5", "R", 270, "5 GND")])
box("J4", 40, 700, 130, 110, "cola 20 pines", [("1", "R", 40, "1 GND"), ("2", "R", 65, "2 K"), ("3", "R", 90, "3 +12")])
label("GND", "J4.1"); label("K_LINE", "J4.2"); label("VBAT_RAW", "J4.3")
T(40, 830, "al conector redondo: 19 GND, 15+17+20 K, 16 (KL15) o 14 (KL30) +12", 9.5, color="#555")
part2("F1", "F", 270, 210, "H"); part2("D1", "Z", 340, 290, "V"); part2("D2", "D", 470, 210, "H")
box("U2", 640, 170, 130, 130, "AP63203 3V3", [("3", "L", 55, "VIN"), ("2", "L", 80, "EN"), ("1", "L", 110, "FB"),
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# UVLO: EN del buck por divisor desde VBAT_F, con hysteresis interna; VBUS lo fuerza a encendido
wire("EN_BUCK", ["U2.2", (580, 250), (580, 300), (560, 300)]); wire("EN_BUCK", ["R10.2", "R11.1"]); wire("EN_BUCK", ["R12.2", (600, 300), (560, 300)])
dot(560, 300, "EN_BUCK"); T(586, 296, "EN_BUCK", 9.5, "start", col("EN_BUCK"), 600)
label("VBAT_F", "R10.1", -20, 0, "L"); label("GND", "R11.2"); label("VBUS", "R12.1", -20, 0, "L")
label("GND", "C10.2"); label("GND", "C11.2"); label("GND", "C12.2"); label("GND", "U2.4")
wire("BST", ["U2.6", (830, 225), "C13.1"]); dot(830, 225, "BST")
wire("SW", ["U2.5", (830, 250), "L1.1"]); wire("SW", ["C13.2", (830, 250)]); dot(830, 250, "SW")
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label("GND", "C14.2"); label("GND", "C15.2")
# --- L9637D
label("+3V3", "U1.3", 40, 0); wire("+3V3", [(490, 610), (520, 610), "C1.1"]); dot(490, 610, "+3V3")
wire("K_RX", ["U1.1", (500, 640)]); label("K_RX", "U1.1", 28, 0)
wire("K_TX", ["U1.4", (500, 670)]); label("K_TX", "U1.4", 28, 0)
label("GND", "U1.5", 10, 0); label("GND", "C1.2")
T(255, 664, "nc", 9, "start", "#888"); T(255, 689, "nc", 9, "start", "#888")
# --- divisor de sensado
label("VBAT_F", "R2.1", 0, -20, "T"); wire("V_SENSE", ["R2.2", (300, 835), "R3.1"]); wire("V_SENSE", [(300, 835), (360, 835), "C3.1"])
dot(300, 835, "V_SENSE"); T(372, 830, "V_SENSE", 10, "start", col("V_SENSE"), 600)
label("GND", "R3.2"); label("GND", "C3.2")
# --- USB
wire("VBUS", ["J3.A4", (790, 610), "J3.A9"]); wire("VBUS", [(790, 615), "D3.2"]); dot(790, 615, "VBUS")
label("VIN", "D3.1")
wire("USB_DP", ["J3.A6", (790, 665), "J3.B6"]); label("USB_DP", "J3.A6", 40, 0)
wire("USB_DN", ["J3.A7", (790, 715), "J3.B7"]); label("USB_DN", "J3.A7", 40, 0)
wire("CC1", ["J3.A5", (800, 765), "R5.1"]); wire("CC2", ["J3.B5", (840, 785), "R6.1"])
label("GND", "R5.2"); label("GND", "R6.2")
wire("GND", ["J3.A1", (580, 750), "J3.A12"]); wire("GND", [(580, 770), "J3.SH"]); label("GND", "J3.SH", -30, 0)
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wire("EN", ["U3.3", (940, 490), "SW1.1"]); wire("EN", ["R4.2", (1060, 490)]); wire("EN", ["C7.1", (1000, 490)])
dot(1060, 490, "EN"); dot(1000, 490, "EN"); T(900, 486, "EN", 10, "end", col("EN"), 600)
label("GND", "C5.1"); label("GND", "C6.2"); label("GND", "C7.2"); label("GND", "SW1.2")
label("V_SENSE", "U3.4", -30, 0, "L"); label("K_TX", "U3.10", -30, 0, "L"); label("K_RX", "U3.11", -30, 0, "L")
label("USB_DN", "U3.13", -30, 0, "L"); label("USB_DP", "U3.14", -30, 0, "L")
wire("GND", ["U3.1", (1070, 800), (1070, 840), "U3.41"]); wire("GND", ["U3.40", (1070, 820)]); label("GND", "U3.41", -30, 0)
wire("IO0", ["U3.27", (1400, 450), "R9.2"]); wire("IO0", [(1440, 450), "SW2.1"]); dot(1400, 450, "IO0"); dot(1440, 450, "IO0")
label("+3V3", "R9.1", 0, -20, "T"); label("GND", "SW2.2"); T(1350, 446, "IO0", 10, "start", col("IO0"), 600)
wire("IO38", ["U3.31", "R8.1"]); wire("LED2_A", ["R8.2", (1470, 530), "LED2.2"]); label("GND", "LED2.1", 0, -20 if False else 0)
label("TXD0", "U3.37", 30, 0); label("RXD0", "U3.36", 30, 0)
label("+3V3", "R7.1", -20, 0, "L"); wire("LED1_A", ["R7.2", (1470, 720), "LED1.2"]); label("GND", "LED1.1")
label("EN", "J2.1", -20, 0, "L"); label("IO0", "J2.2", -20, 0, "L"); label("TXD0", "J2.3", -20, 0, "L")
label("RXD0", "J2.4", -20, 0, "L"); label("GND", "J2.5", -20, 0); label("+3V3", "J2.6", -20, 0, "L")
wire("GND", ["J1.4", (200, 390), "J1.5"]); label("GND", "J1.5", 20, 0)

# ------------------------------------------------------------------ notas
T(40, 40, "E36 K-line reader — ESP32-S3 + L9637D + AP63203, una sola placa (rev B)", 16, weight=600)
T(40, 60, "GND, +3V3, VIN y VBAT_F se conectan por etiqueta. LED2 anodo(2)->R8; catodos (pin 1) a GND. D1: banda (pin 1) a VBAT_F.", 10.5, color="#555")
T(40, 76, "K va a OBD2 7 Y 15 (linea L): el DME del E36 despierta por L. R1 510R 0,75W = pull-up K a VS (RKO <= 5k por hoja de datos).", 10.5, color="#555")
T(40, 92, "USB VBUS y 12V se OR-ean por D2/D3 hacia VIN; el buck saca 3V3 directo. R10/R11 = UVLO del buck: arranca a 12,5 V y corta a 11,5 V; R12 hace que con USB arranque siempre.", 10.5, color="#555")

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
